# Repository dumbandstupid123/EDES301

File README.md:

# EDES301

EDES 301: Introduction to Practical Electrical Engineering (Fall 2025) @ Rice University 
Taught By: Dr. Erik Welsh

This is a cumulative repository of all assignments, projects, and required documentation

Repo Content:
- Homework 1: Circuit Analysis
- Homework 2: Pocket Beagle Introduction and Setup
- Homework 3: Packages, Internet + Binary
- Homework 4: Python for Embedded Systems 

Project 1:
- Initial Project Proposal
- System Design + Software Documentation
- Relevant Project Code

Project 2:
- Mechanical Block Diagram
- Library
- Schematics 
- Complete Printed Circuit Board Design (Designed for Non Invasive Glucose Signal Processing + Reading)

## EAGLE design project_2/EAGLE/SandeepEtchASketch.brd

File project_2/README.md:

## EDES301 Project 2: Digital Etch-A-Sketch PCB

## Project Overview
This project involves the design and layout of a custom Printed Circuit Board (PCB) for a digital Etch-A-Sketch system. The board interfaces a microcontroller development board with an SPI LCD screen, analog inputs for drawing control, and digital inputs for system commands.

This design was created using Autodesk EAGLE as part of the EDES301 course requirements.

## Hardware Specifications
The PCB connects the following components to the main microcontroller:
* **Display:** Interface for Adafruit SPI LCD Screen (Model 1770 or similar).
* **User Input:**
    * 2x Potentiometers (Control for X and Y axis drawing).
    * 2x Push Buttons (For "Clear Screen" or mode selection).
* **Status Indicators:** Red, Green, and Blue LEDs for system status feedback.
* **Storage:** MicroSD card slot for saving drawings or loading assets.
* **Host:** Headers for NUCLEO development board connection.

## Manufacturing
The board is designed with standard 2-layer constraints:
* **Trace Width:** 10 mil (Signal) / 15 mil (Power).
* **Vias:** 12 mil drill / 24 mil diameter.
* **Fabrication:** Files are formatted for standard CAM processing (Gerber RS-274X).

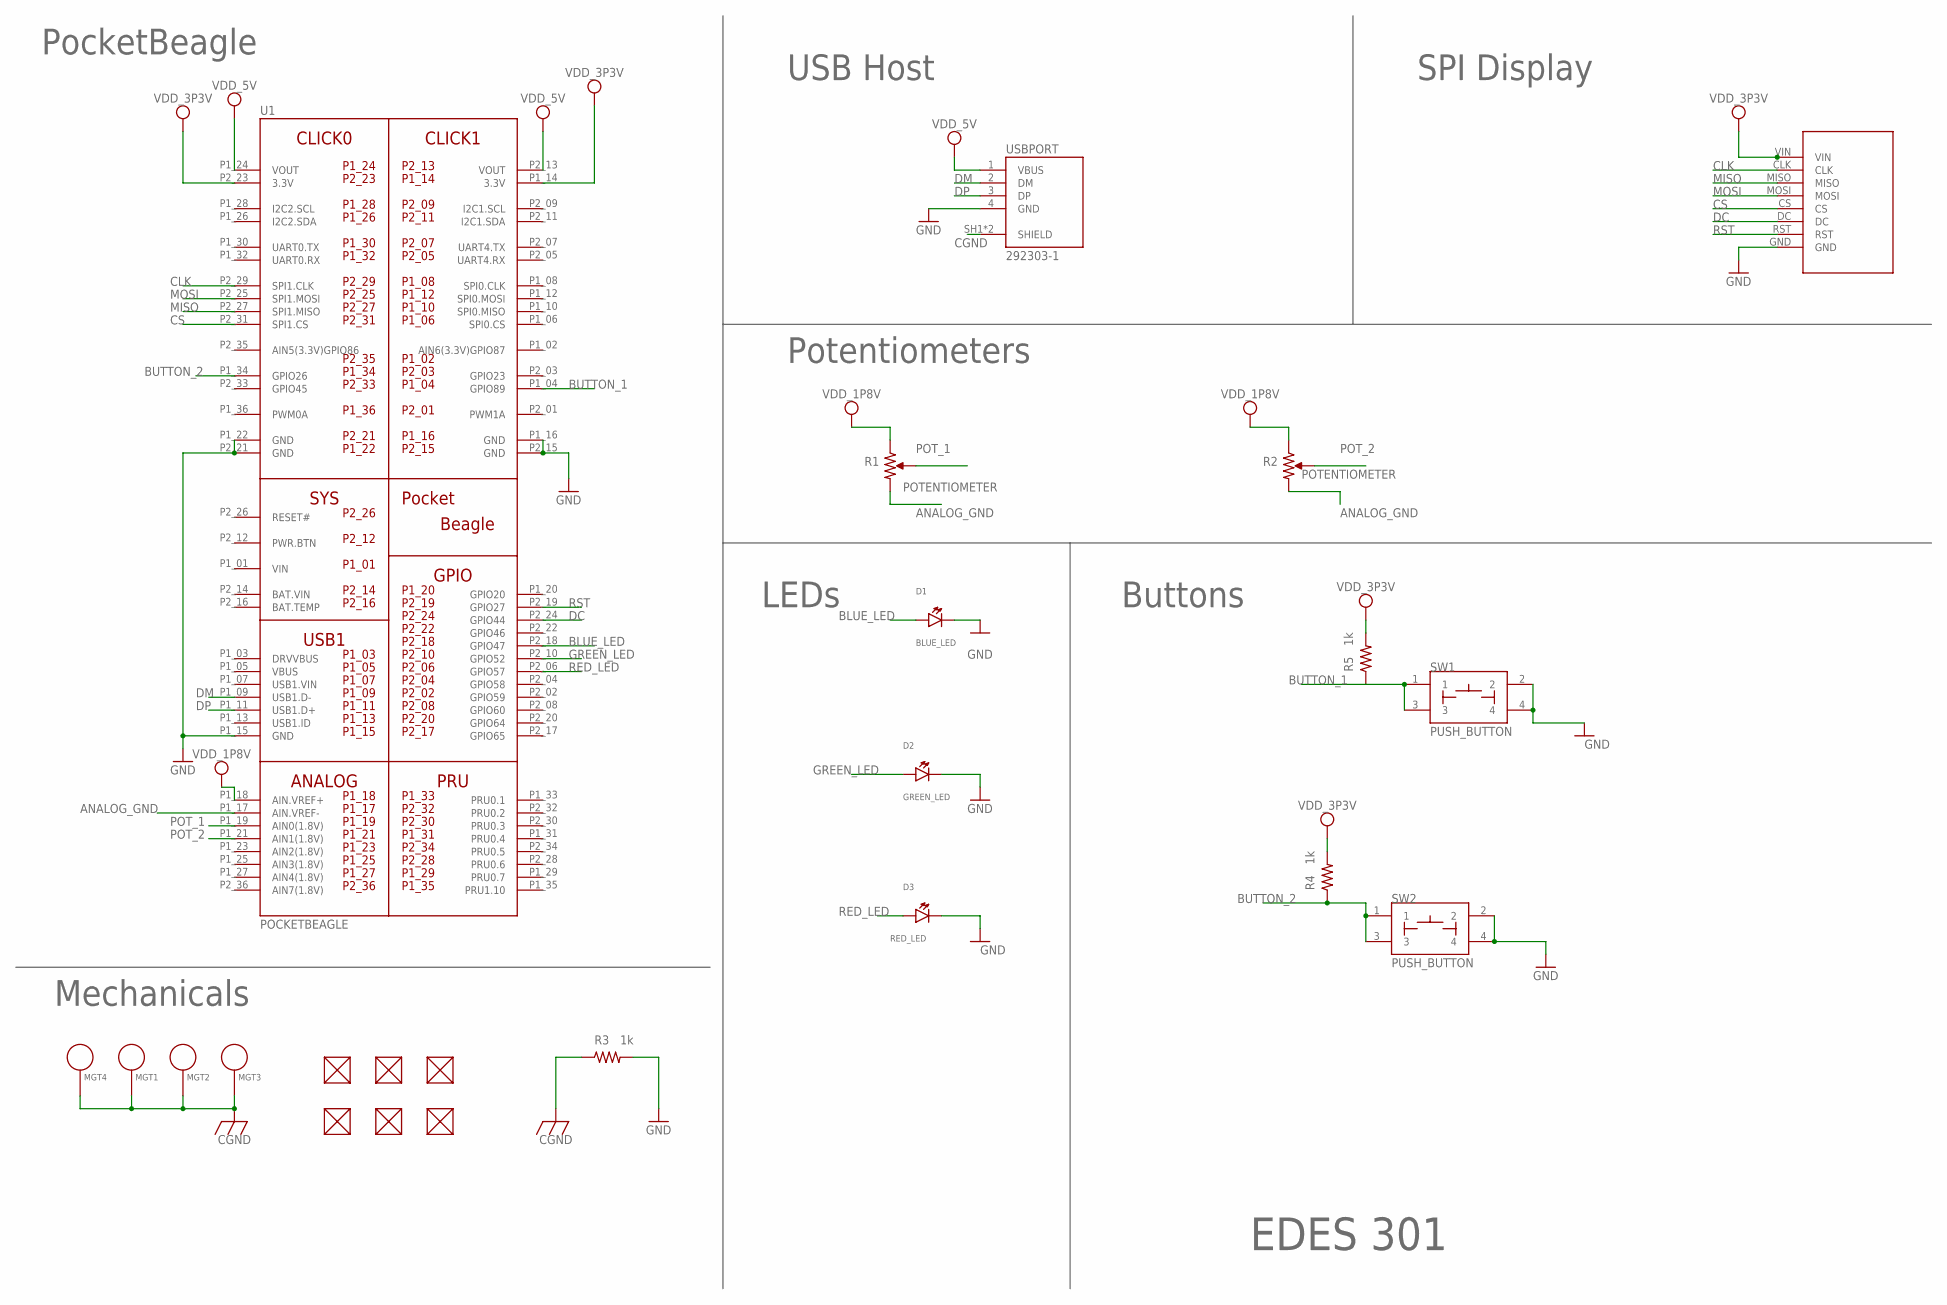
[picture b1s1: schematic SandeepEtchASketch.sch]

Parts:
D1: BLUE_LED; EIA-STD
D2: GREEN_LED; EIA-STD
D3: RED_LED; EIA-STD
FUD1, FUD2, FUD3, FUD4, FUD5, FUD6: FIDUCIAL; FIDUCIAL_40MIL
MGT1, MGT2, MGT3, MGT4: MOUNTING_HOLE
R1, R2: POTENTIOMETER; POT-PO90S
R3, R4, R5: 1k; R0603
SPIDISPLAY: SCREEN
SW1, SW2: PUSH_BUTTON; BUTTON_12.5MM
U1: POCKETBEAGLE
USBPORT: 292303-1; TE_292303-1

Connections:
ANALOG_GND: R1.CW, R2.CW, U1.P1_17 (AIN.VREF-)
BAT.VIN: U1.P2_14 (BAT.VIN)
BLUE_LED: D1.ANODE, U1.P2_18 (GPIO47)
BUTTON_1: R5.1, SW1.1, SW1.3, U1.P1_04 (GPIO89)
BUTTON_2: R4.1, SW2.1, SW2.3, U1.P1_34 (GPIO26)
CGND: MGT1.P$1, MGT2.P$1, MGT3.P$1, MGT4.P$1, R3.1, USBPORT.SH1 (SHIELD), USBPORT.SH2 (SHIELD)
CLK: SPIDISPLAY.CLK, U1.P2_29 (SPI1.CLK)
CS: SPIDISPLAY.CS, U1.P2_31 (SPI1.CS)
DC: SPIDISPLAY.DC, U1.P2_24 (GPIO44)
DM: U1.P1_09 (USB1.D-), USBPORT.2 (DM)
DP: U1.P1_11 (USB1.D+), USBPORT.3 (DP)
GND: D1.CATHODE, D2.CATHODE, D3.CATHODE, R3.2, SPIDISPLAY.GND, SW1.2, SW1.4, SW2.2, SW2.4, U1.P1_15 (GND), U1.P1_16 (GND), U1.P1_22 (GND), U1.P2_15 (GND), U1.P2_21 (GND), USBPORT.4 (GND)
GREEN_LED: D2.ANODE, U1.P2_10 (GPIO52)
MISO: SPIDISPLAY.MISO, U1.P2_27 (SPI1.MISO)
MOSI: SPIDISPLAY.MOSI, U1.P2_25 (SPI1.MOSI)
POT_1: R1.S, U1.P1_19 (AIN0(1.8V))
POT_2: R2.S, U1.P1_21 (AIN1(1.8V))
RED_LED: D3.ANODE, U1.P2_06 (GPIO57)
RST: SPIDISPLAY.RST, U1.P2_19 (GPIO27)
VDD_1P8V: R1.CCW, R2.CCW, U1.P1_18 (AIN.VREF+)
VDD_3P3V: R4.2, R5.2, SPIDISPLAY.VIN, U1.P1_14 (3.3V), U1.P2_23 (3.3V)
VDD_5V: U1.P1_24 (VOUT), U1.P2_13 (VOUT), USBPORT.1 (VBUS)
VIN: U1.P1_01 (VIN)

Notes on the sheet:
PocketBeagle
SPI Display
USB Host
Potentiometers
LEDs
Buttons
Mechanicals
EDES 301

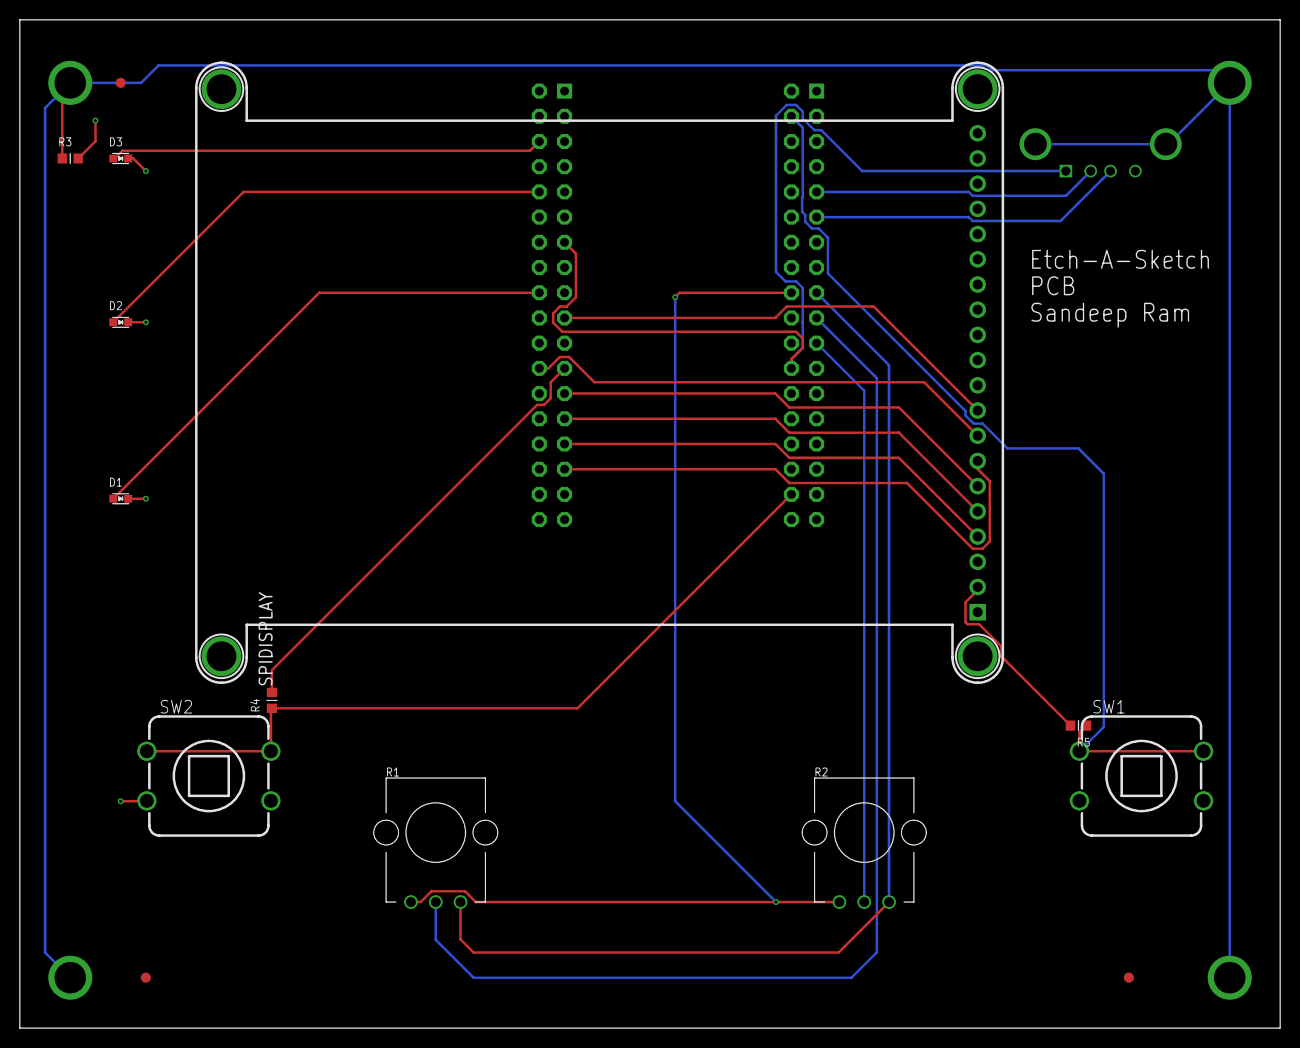
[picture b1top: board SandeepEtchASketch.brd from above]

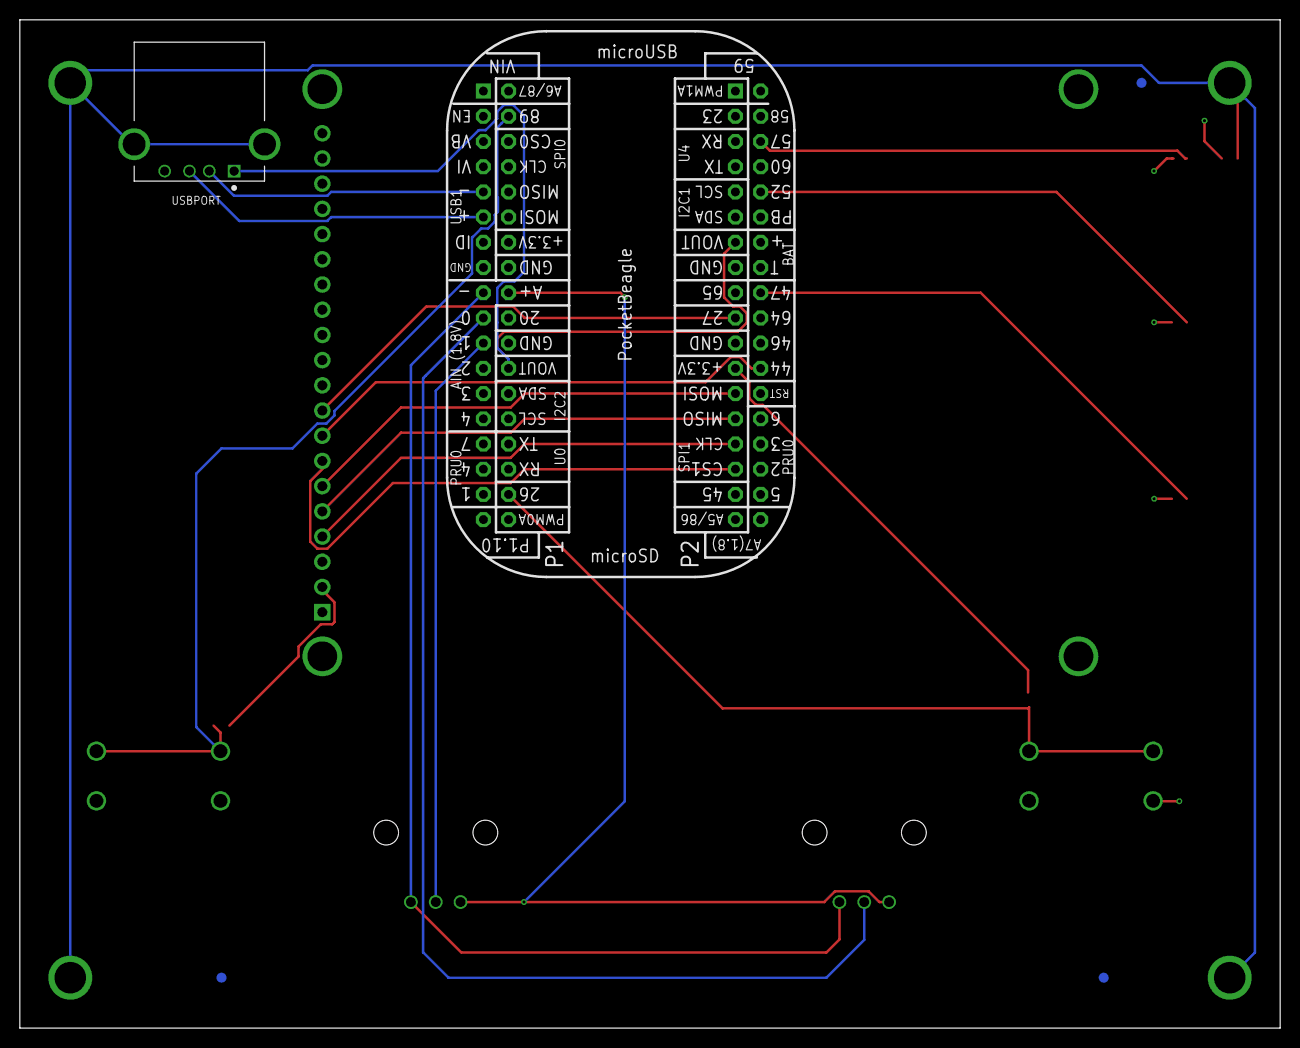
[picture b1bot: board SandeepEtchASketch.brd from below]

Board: 4 copper layers, 127.0 x 101.6 mm, 23 parts (5 on the bottom side), 21 nets.

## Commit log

2025-10-06 Create project_01
2025-10-06 Sandeep Ramlochan project proposal
2025-12-15 Add README with course information
2025-12-15 Enhance README with course info and assignments
    Expanded the README to include course details and repo content.
2025-12-15 Fix formatting issues in README.md
2025-12-15 Rename Note 16 Sep 2025.pdf to Homework 1
2025-12-15 Rename <Sandeep_Ramlochan>_EDES301_project_01_proposal.pptx..key to Project One Proposal Presentation
2025-12-15 Create Homework 2
2025-12-15 Rename Homework 1 to Homework_1.pdf
2025-12-15 Create non
2025-12-15 EDES_301_project_2.pdf
2025-12-15 Add Project 1: Pocket Radar System
2025-12-15 Create new
2025-12-15 Add content to new survey file
2025-12-16 Update README to include homework assignments
    Added homework assignments to the README.
2025-12-16 Create python
2025-12-16 Create simple_calc
2025-12-16 Implement LED blinking functionality for USR3
    Added a simple program to blink USR LED 3 at 5Hz.
2025-12-16 Add Button class with callback support
    This commit introduces a new Button class that supports both pull-up and pull-down resistor configurations. It includes methods for checking button state, waiting for presses, and setting callback fu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
2025-12-16 Create project_1: pocket radar
2025-12-16 Revise README for Pocket Radar project
    Updated README.md to improve clarity and formatting.
2025-12-16 Revise README.md for improved readability
    Updated formatting and structure of README.md for clarity.
2025-12-16 Add radar engine and web server for sonar control
    Implement radar functionality with web interface and servo control.
2025-12-16 Update README with project introduction
    Added a brief introduction to the Pocket Radar project.
2025-12-16 Fix formatting in README.md
2025-12-16 Update README with Cloud9 IDE setup instructions
    Added setup instructions for connecting to Cloud9 IDE.
2025-12-16 Update README with project details and resources
    Added project description and Hackster page link.
2025-12-16 Update README.md to remove image and add license
    Removed an image and added a license section.
2025-12-16 Clean up README by removing duplicate image
    Removed duplicate image from README and adjusted formatting.
2025-12-16 Create rasputia
2025-12-16 Rename mech_design.pdf to mechanical_block_diagram.pdf
2025-12-16 Create boh
2025-12-16 Rename joshua.pdf.png to etch_block_schematics.png
2025-12-19 Create bloh
2025-12-19 Create blog
2025-12-19 Add Eagle PCB files to project_02/EAGLE
2025-12-19 Create n
2025-12-19 Create merry
2025-12-19 Create lol
2025-12-19 Rename Etch.brd to etch.brd
2025-12-19 Create log
2025-12-19 Add pnp_front.txt with component specifications
    Added components for blue, green, and red LEDs, fiducials, and resistors.
2025-12-19 Add etch.txt with partlist from EAGLE design
2025-12-19 Create files
2025-12-19 Create bleh
2025-12-19 Create blank
2025-12-19 Create bop
2025-12-19 Create mon
2025-12-19 Create lll
2025-12-19 Create mkm
2025-12-19 Add BOM for EtchASketch project
2025-12-19 Change header format in README.md
2025-12-19 Update README to remove repository structure details
    Removed repository structure section from README.
2025-12-19 Rename etched.pdf.png to schematic.png
